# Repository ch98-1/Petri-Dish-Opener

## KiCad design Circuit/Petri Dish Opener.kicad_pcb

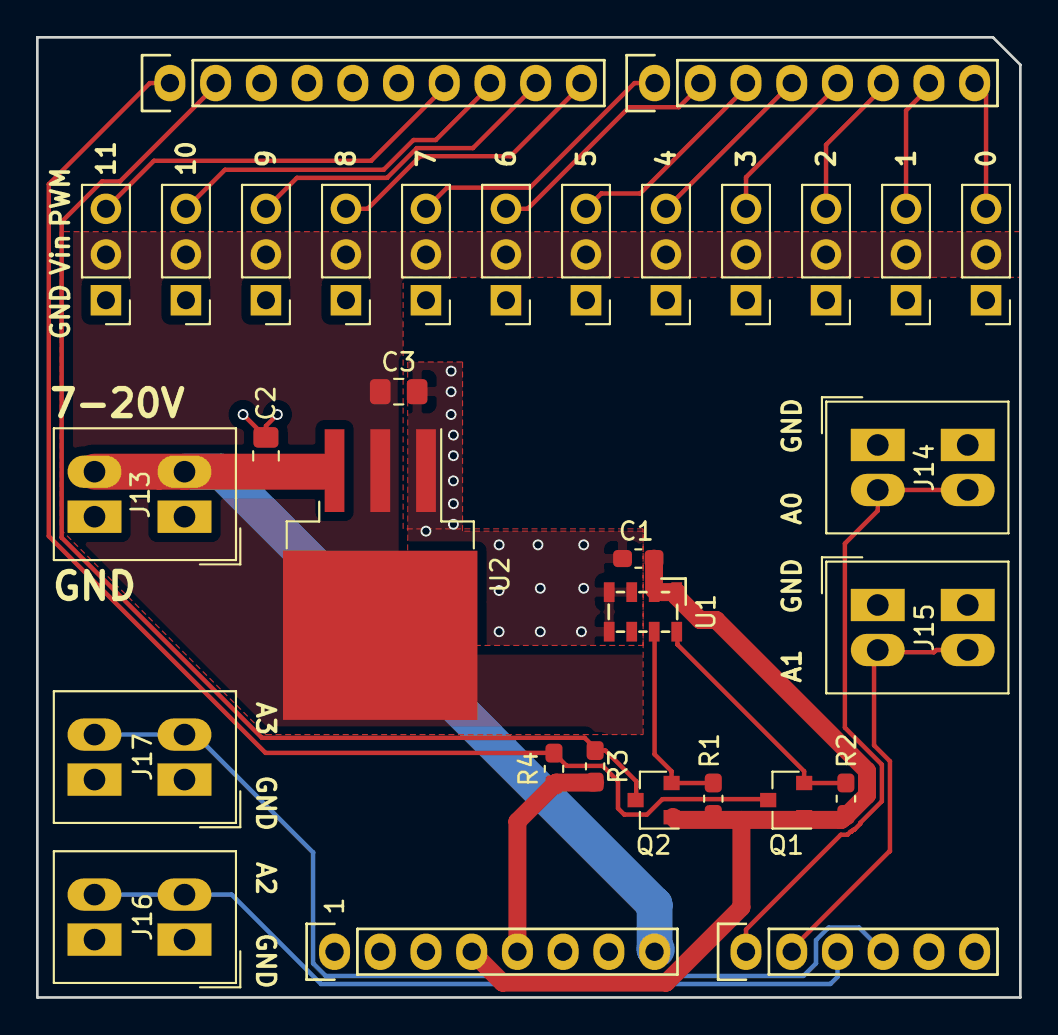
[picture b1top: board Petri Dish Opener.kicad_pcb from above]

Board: 2 copper layers, 54.6 x 53.3 mm, 32 parts (0 on the bottom side), 25 nets.

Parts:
C1: 100nF; C_0603_1608Metric_Pad1.05x0.95mm_HandSolder
C2, C3: 22uF; C_0805_2012Metric_Pad1.15x1.40mm_HandSolder
J1, J2, J3, J4, J5, J6, J7, J8, J9, J10, J11, J12: Conn_01x03_Male; PinHeader_1x03_P2.54mm_Vertical
J13, J14, J15, J16, J17: Conn_01x02_Female; TerminalBlock_Phoenix_PTSM-0,5-2-2.5-H-THR_1x02_P2.50mm_Hor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
P1: Power; Socket_Strip_Arduino_1x08
P2: Analog; Socket_Strip_Arduino_1x06
P3: Digital; Socket_Strip_Arduino_1x10
P4: Digital; Socket_Strip_Arduino_1x08
Q1, Q2: BSS138; SOT-23
R1, R2, R3, R4: 10k; R_0603_1608Metric_Pad1.05x0.95mm_HandSolder
U1: MS5607
U2: LM1084-5.0; TO-263-3_TabPin2

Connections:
+3V3: C1.1, P1.4, Q1.1, Q2.1, R1.1, R2.1, U1.1, U1.2
+5V: P1.5, R3.1, R4.1
+5VD: C3.1, J1.2, J2.2, J3.2, J4.2, J5.2, J6.2, J7.2, J8.2, J9.2, J10.2, J11.2, J12.2, U2.2
/0(Rx): J12.3, P4.8
/1(Tx): J11.3, P4.7
/2: J10.3, P4.6
/3(**): J9.3, P4.5
/4: J8.3, P4.4
/5(**): J7.3, P4.3
/6(**): J6.3, P4.2
/7: J5.3, P4.1
/8: J4.3, P3.10
/9(**): J3.3, P3.9
/10(**/SS): J2.3, P3.8
/11(**/MOSI): J1.3, P3.7
/A0: J14.2, P2.1
/A1: J15.2, P2.2
/A2: J16.2, P2.3
/A3: J17.2, P2.4
/A4(SDA): P2.5, P3.2, Q2.3, R3.2
/A5(SCL): P2.6, P3.1, Q1.3, R4.2
/Vin: C2.1, J13.2, P1.8, U2.3
GND: C1.2, C2.2, C3.2, J1.1, J2.1, J3.1, J4.1, J5.1, J6.1, J7.1, J8.1, J9.1, J10.1, J11.1, J12.1, J13.1, J14.1, J15.1, J16.1, J17.1, P1.6, P1.7, P3.4, U1.3, U1.4, U1.5, U2.1
unnamed: Q1.2, R2.2, U1.8
unnamed: Q2.2, R1.2, U1.7

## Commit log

2019-08-06 Initial files
2019-08-06 Updated text on pcb
2019-08-06 added file to gitignore
2019-08-06 Added the code and edited the board a bit
2019-08-07 Wrote up the code for analog pressure sensor
2019-08-07 updated comment
2019-08-07 Fixed error in pressure calculation
2019-08-07 cleaned up some part of the code
2019-08-07 added altitude averaging to reduce read noise
2019-08-07 Updated to use different averaging numbers depending on pressure sensor in use
2019-08-09 Added more servos for testing
2019-08-09 Added debug report feture
2019-08-09 disable debug mode for default
2019-08-14 cleaned up code a bit
2019-08-22 Changed mistake in component
2019-08-22 Changed to 6AA isntead of 1 9V
2019-08-22 added individual angle control
2019-08-23 Using better altitude estimation, and changed default altitudes to what was requested
